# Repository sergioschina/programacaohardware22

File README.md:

# programação de Hardware 22

Repositorio dedicado a materia de arquitetura de hardware 22

Neste repositório, será realizado a entrega de todos os trabalhos de programação de hardware de 2022.

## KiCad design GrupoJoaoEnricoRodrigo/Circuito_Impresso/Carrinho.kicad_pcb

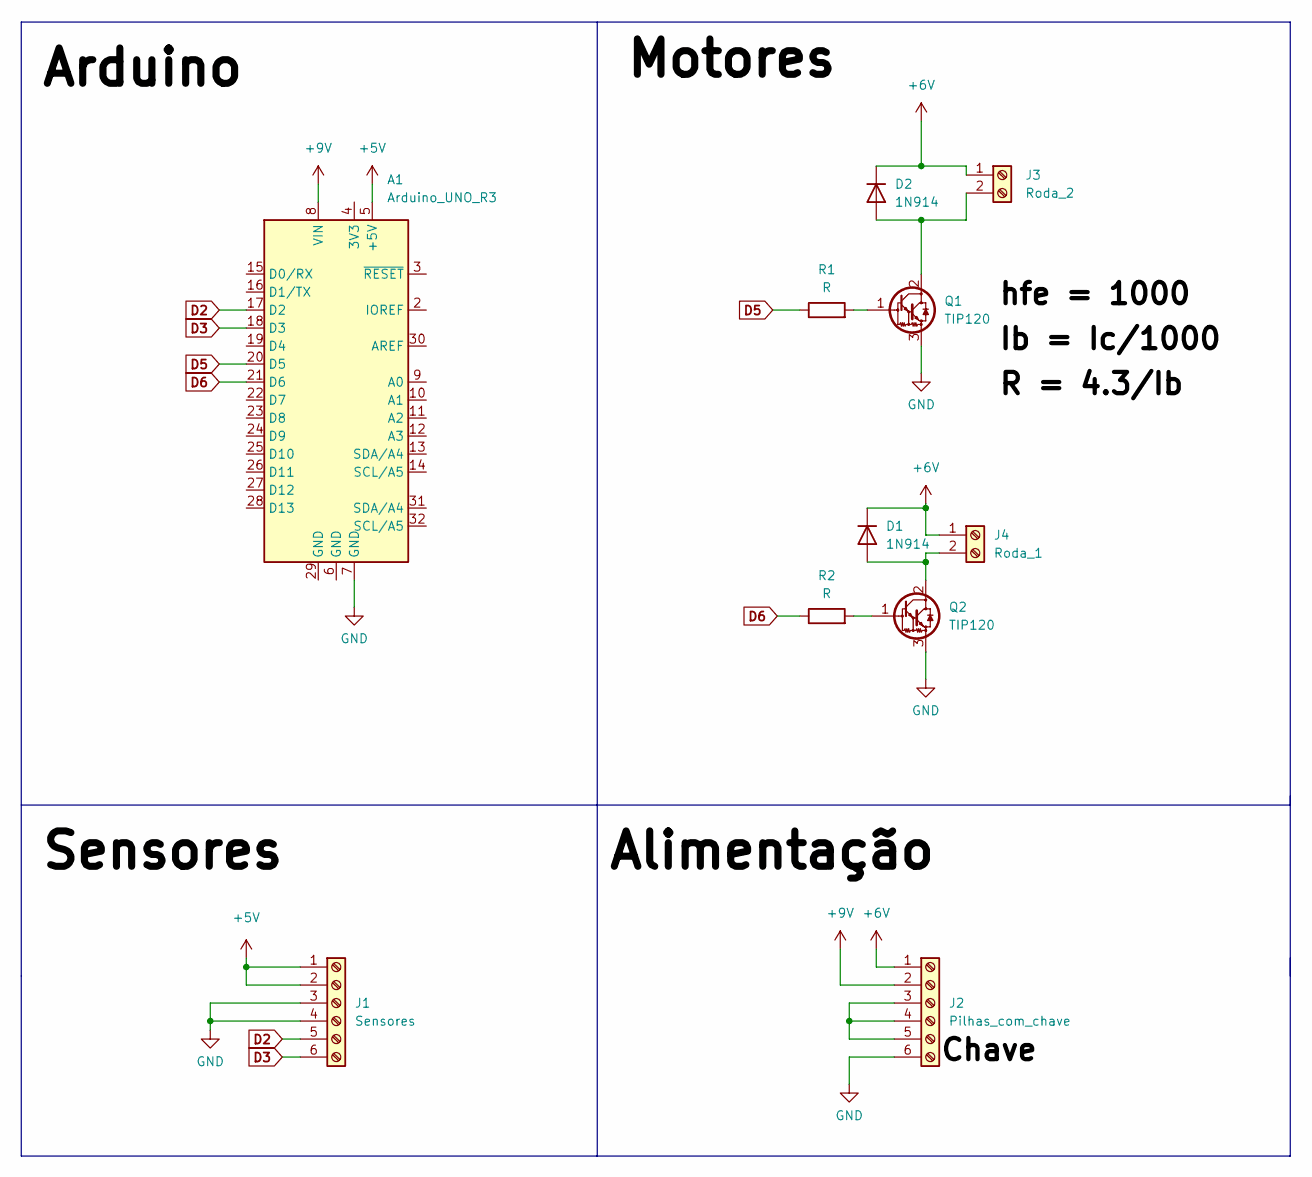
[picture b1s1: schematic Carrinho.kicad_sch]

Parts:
A1: Arduino_UNO_R3
D1, D2: 1N914; D_DO-35_SOD27_P7.62mm_Horizontal
J1: Sensores; TerminalBlock_bornier-6_P5.08mm
J2: Pilhas_com_chave; TerminalBlock_bornier-6_P5.08mm
J3: Roda_2; TerminalBlock_Altech_AK300-2_P5.00mm
J4: Roda_1; TerminalBlock_Altech_AK300-2_P5.00mm
Q1, Q2: TIP120; TO-220-3_Vertical
R1, R2: R; R_Axial_DIN0207_L6.3mm_D2.5mm_P15.24mm_Horizontal

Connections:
+5V: A1.5 (+5V), J1.1, J1.2
+6V: D1.1 (K), D2.1 (K), J2.1, J3.1, J4.1
+9V: A1.8 (VIN), J2.2
D2: A1.17 (D2), J1.5
D3: A1.18 (D3), J1.6
D5: A1.20 (D5), R1.1
D6: A1.21 (D6), R2.1
GND: A1.7 (GND), J1.3, J1.4, J2.6, Q1.3 (E), Q2.3 (E)
unnamed: D2.2 (A), J3.2, Q1.2 (C)
unnamed: J2.3, J2.4, J2.5
unnamed: D1.2 (A), J4.2, Q2.2 (C)
unnamed: Q1.1 (B), R1.2
unnamed: Q2.1 (B), R2.2

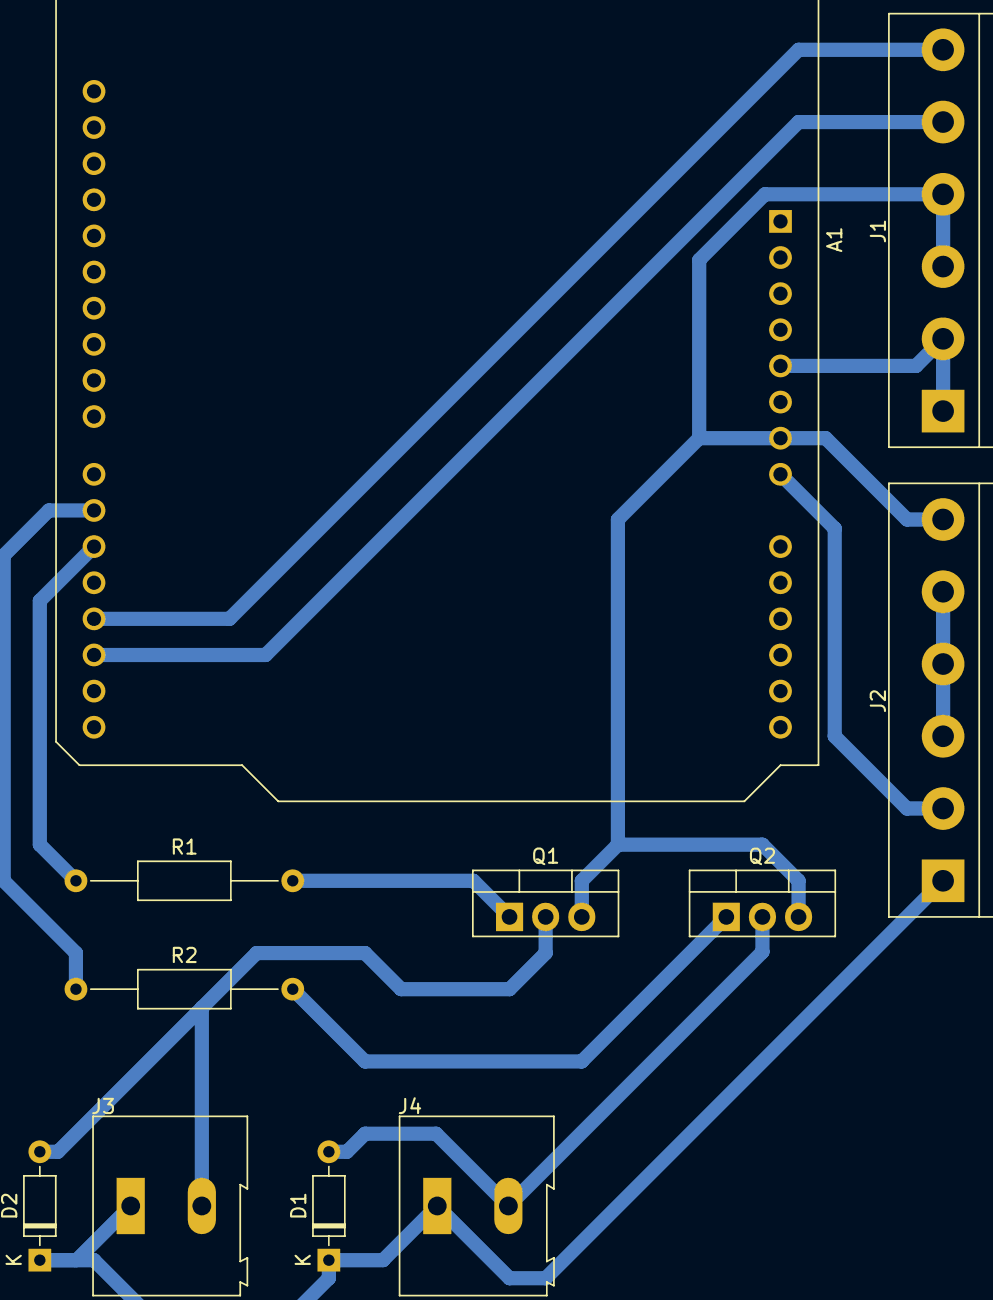
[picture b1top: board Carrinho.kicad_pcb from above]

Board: 2 copper layers, 11 parts (0 on the bottom side), 13 nets.

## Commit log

2022-11-12 Template Doxygen para projeto
    Este é o modelo de template para se ter uma documentação mínima de código.
2022-11-12 primeiro commit
2022-11-12 deixaseujooj
2022-11-12 Primeiro commit do grupo
2022-11-12 Update TXT grupo
2022-11-12 Grupo carrinho W.F.T
2022-11-12 tooop
2022-11-12 commit do grupo
2022-11-12 Group add
2022-11-12 Grupo Felipe-Geovanne-Nickolas-Victor
2022-11-18 Código do projeto
2022-11-19 #1 [Add] - Adding all docs
2022-11-19 Código do Projeto.
2022-11-19 #2 [Add] - Include CI
2022-11-19 [add]: adding all project files
2022-11-19 Código Fonte
2022-11-19 update code
2022-11-19 commit projeto seguidor linha
2022-11-19 Seguidor de linha FGNV
